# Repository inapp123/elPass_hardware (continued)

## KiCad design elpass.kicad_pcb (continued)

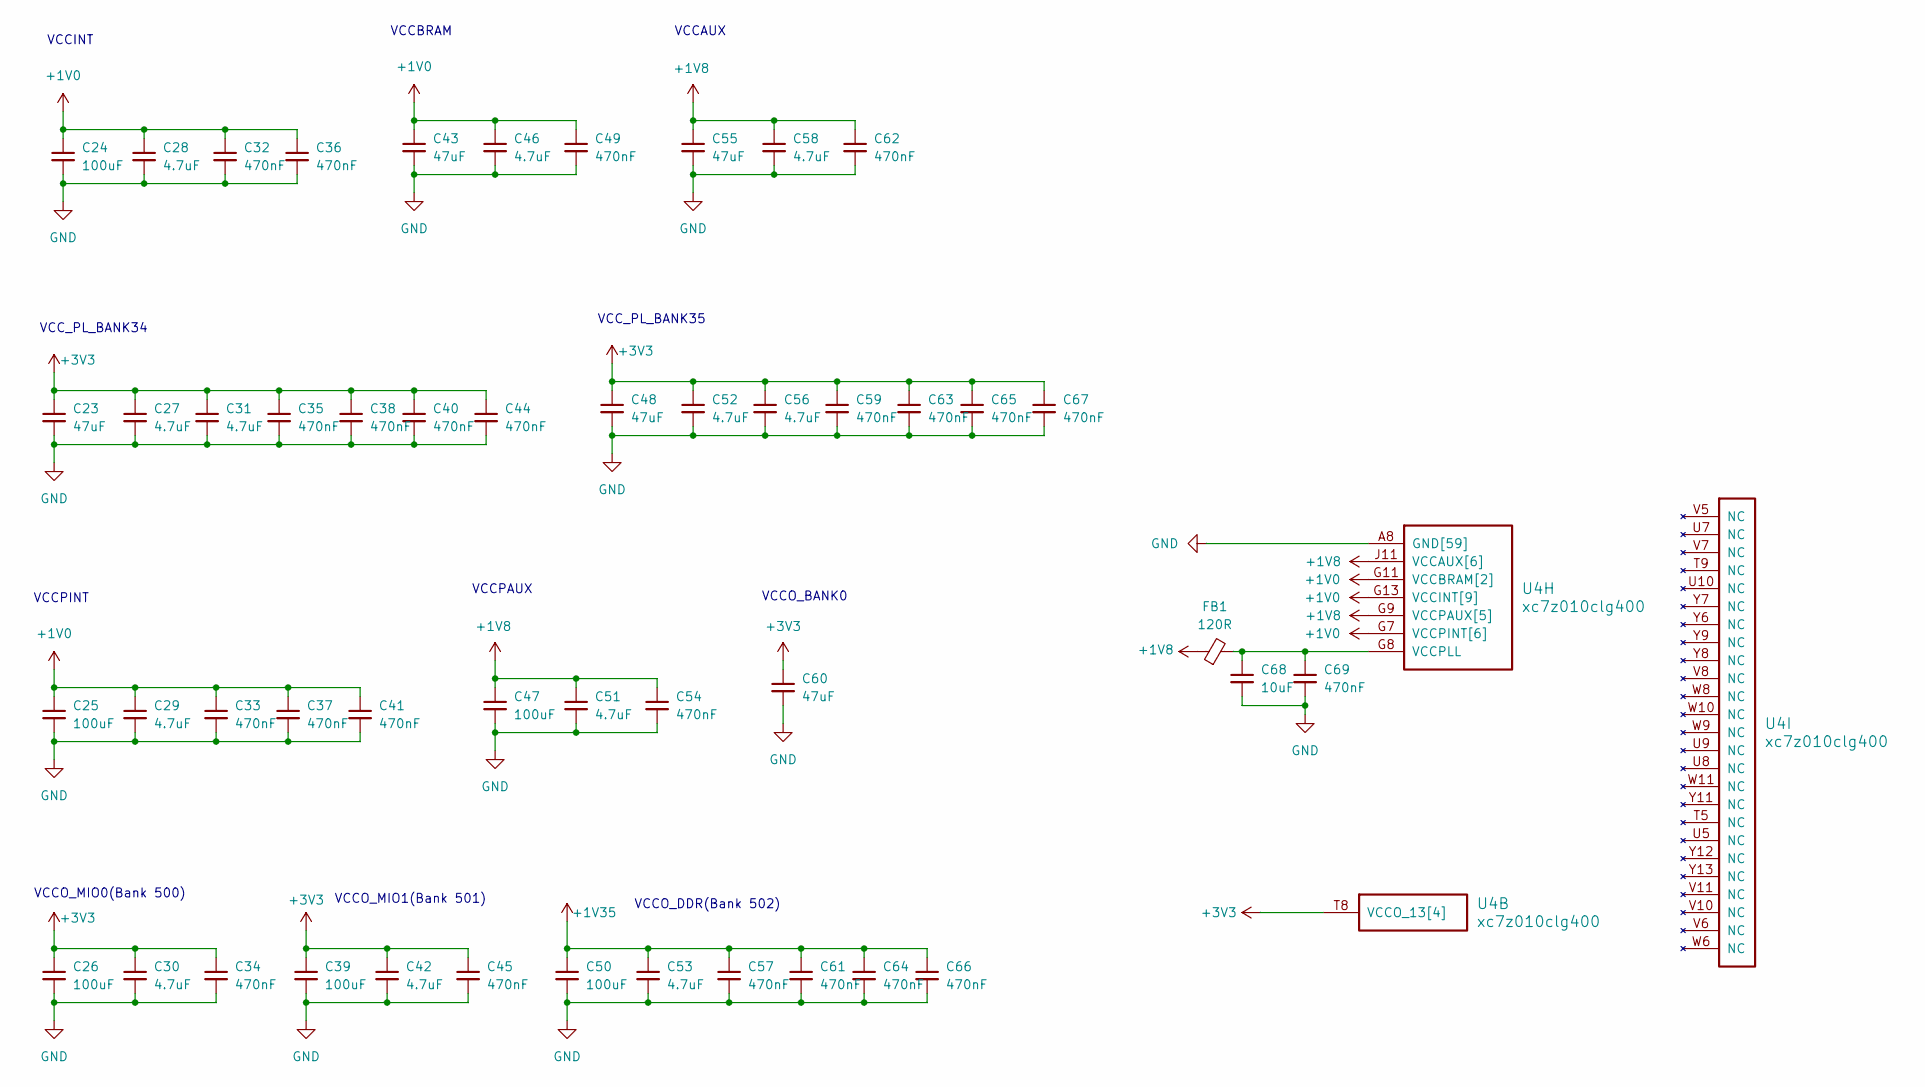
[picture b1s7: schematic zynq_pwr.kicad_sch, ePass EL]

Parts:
C23, C43, C48, C55, C60: 47uF; C_0603_1608Metric
C24, C25, C26, C39, C47, C50: 100uF; C_1206_3216Metric
C27, C28, C29, C30, C31, C42, C46, C51, C52, C53, C56, C58: 4.7uF; C_0402_1005Metric
C32, C33, C35, C36, C37, C38, C40, C41, C44, C45, C49, C54, C57, C59, C61, C62, C63, C64, C65, C67, C69: 470nF; C_0201_0603Metric
C34, C66: 470nF; C_0201_0603Metric_WideGap
C68: 10uF; C_0805_2012Metric
FB1: 120R; L_0603_1608Metric
U4: xc7z010clg400; Xilinx_CLG400_NoPaste_JLC_Package_Delay

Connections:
+1V0: C24.1, C25.1, C28.1, C29.1, C32.1, C33.1, C36.1, C37.1, C41.1, C43.1, C46.1, C49.1, U4.G7 (VCCPINT[6]), U4.G11 (VCCBRAM[2]), U4.G13 (VCCINT[9]), U4.H10 (VCCBRAM[2]), U4.H12 (VCCINT[9]), U4.J7 (VCCPINT[6]), U4.J13 (VCCINT[9]), U4.K12 (VCCINT[9]), U4.L7 (VCCPINT[6]), U4.L13 (VCCINT[9]), U4.M12 (VCCINT[9]), U4.N7 (VCCPINT[6]), U4.N13 (VCCINT[9]), U4.P8 (VCCPINT[6]), U4.P12 (VCCINT[9]), U4.R7 (VCCPINT[6]), U4.R13 (VCCINT[9]); also elsewhere on the board
+1V8: C47.1, C51.1, C54.1, C55.1, C58.1, C62.1, FB1.1, U4.F8 (VCCPAUX[5]), U4.G9 (VCCPAUX[5]), U4.H8 (VCCPAUX[5]), U4.J11 (VCCAUX[6]), U4.K8 (VCCPAUX[5]), U4.L11 (VCCAUX[6]), U4.M8 (VCCPAUX[5]), U4.N9 (VCCAUX[6]), U4.N11 (VCCAUX[6]), U4.P10 (VCCAUX[6]), U4.R9 (VCCAUX[6]); also elsewhere on the board
+1V35: C50.1, C53.1, C57.1, C61.1, C64.1, C66.1; also elsewhere on the board
+3V3: C23.1, C26.1, C27.1, C30.1, C31.1, C34.1, C35.1, C38.1, C39.1, C40.1, C42.1, C44.1, C45.1, C48.1, C52.1, C56.1, C59.1, C60.1, C63.1, C65.1, C67.1, U4.T8 (VCCO_13[4]), U4.U11 (VCCO_13[4]), U4.W7 (VCCO_13[4]), U4.Y10 (VCCO_13[4]); also elsewhere on the board
GND: C23.2, C24.2, C25.2, C26.2, C27.2, C28.2, C29.2, C30.2, C31.2, C32.2, C33.2, C34.2, C35.2, C36.2, C37.2, C38.2, C39.2, C40.2, C41.2, C42.2, C43.2, C44.2, C45.2, C46.2, C47.2, C48.2, C49.2, C50.2, C51.2, C52.2, C53.2, C54.2, C55.2, C56.2, C57.2, C58.2, C59.2, C60.2, C61.2, C62.2, C63.2, C64.2, C65.2, C66.2, C67.2, C68.2, C69.2, U4.A8 (GND[59]), U4.A18 (GND[59]), U4.B1 (GND[59]), U4.B11 (GND[59]), U4.C4 (GND[59]), U4.C9 (GND[59]), U4.C14 (GND[59]), U4.D17 (GND[59]), U4.E10 (GND[59]), U4.E20 (GND[59]), U4.F3 (GND[59]), U4.F7 (GND[59]), U4.G10 (GND[59]), U4.G12 (GND[59]), U4.G16 (GND[59]), U4.H7 (GND[59]), U4.H9 (GND[59]), U4.H11 (GND[59]), U4.H13 (GND[59]), U4.H19 (GND[59]), U4.J2 (GND[59]), U4.J8 (GND[59]), U4.J12 (GND[59]), U4.K5 (GND[59]), U4.K7 (GND[59]), U4.K11 (GND[59]), U4.K13 (GND[59]), U4.K15 (GND[59]), U4.L8 (GND[59]), U4.L12 (GND[59]), U4.L18 (GND[59]), U4.M1 (GND[59]), U4.M7 (GND[59]), U4.M11 (GND[59]), U4.M13 (GND[59]), U4.N4 (GND[59]), U4.N8 (GND[59]), U4.N10 (GND[59]), U4.N12 (GND[59]), U4.N14 (GND[59]), U4.P7 (GND[59]), U4.P9 (GND[59]), U4.P11 (GND[59]), U4.P13 (GND[59]), U4.P17 (GND[59]), U4.R8 (GND[59]), U4.R12 (GND[59]), U4.R20 (GND[59]), U4.T3 (GND[59]), U4.T7 (GND[59]), U4.T13 (GND[59]), U4.U6 (GND[59]), U4.U16 (GND[59]), U4.V9 (GND[59]), U4.V19 (GND[59]), U4.W2 (GND[59]), U4.W12 (GND[59]), U4.Y5 (GND[59]), U4.Y15 (GND[59]); also elsewhere on the board
unnamed: C68.1, C69.1, FB1.2, U4.G8 (VCCPLL)

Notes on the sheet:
VCCO_DDR(Bank 502)
VCCBRAM
VCC_PL_BANK34
VCCPINT
VCCINT
VCCAUX
VCCO_MIO0(Bank 500)
VCCO_BANK0
VCCPAUX
VCCO_MIO1(Bank 501)
VCC_PL_BANK35

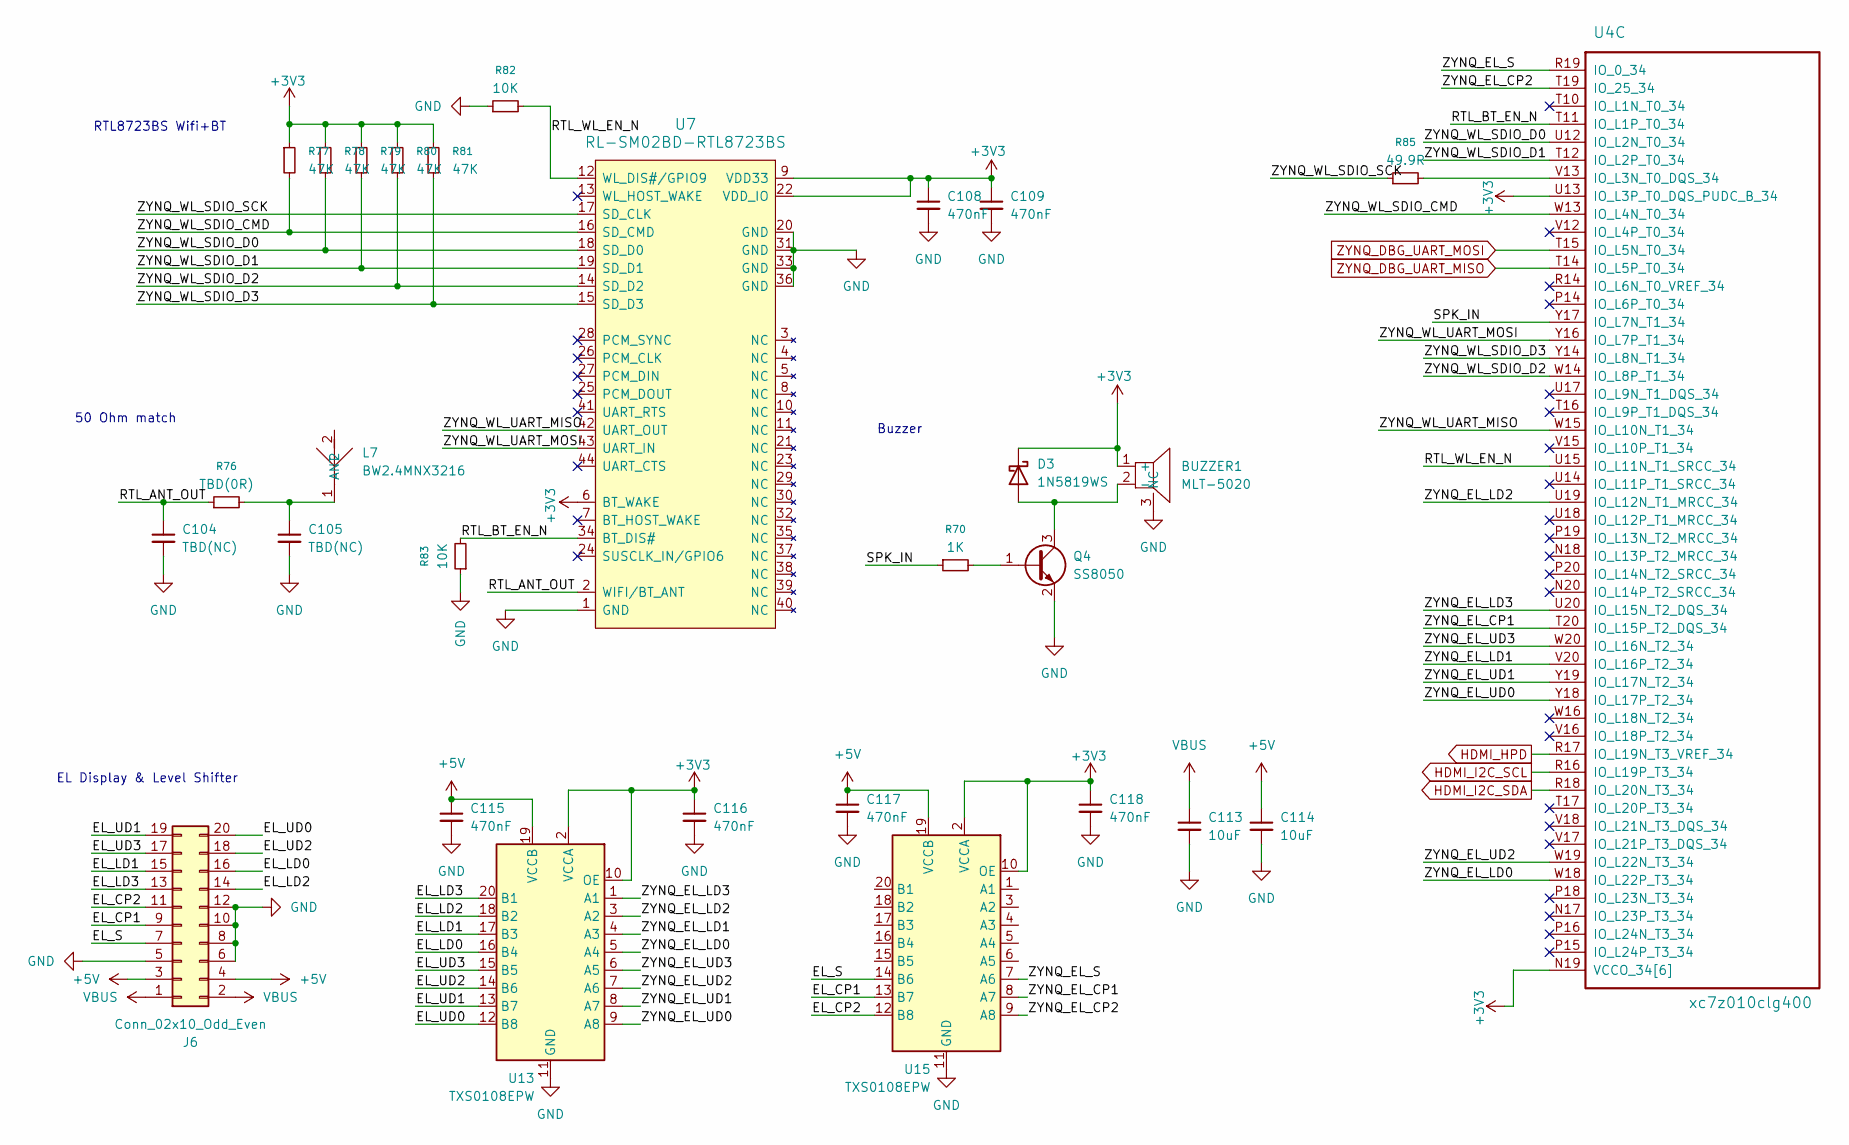
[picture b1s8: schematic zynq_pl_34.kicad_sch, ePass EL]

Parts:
BUZZER1: MLT-5020; BUZ-SMD_L5.0-W5.5-P4.60; MPN MLT-5020; LCSC Part C94598
C104, C105: TBD(NC); C_0402_1005Metric
C108, C109, C115, C116, C117, C118: 470nF; C_0201_0603Metric
C113, C114: 10uF; C_0805_2012Metric
D3: 1N5819WS; D_SOD-323
J6: Conn_02x10_Odd_Even; PinSocket_2x10_P2.00mm_Vertical
L7: BW2.4MNX3216; ANT-SMD_L3.4-W1.8_BW2.4MNX3216; MPN BW2.4MNX3216; LCSC Part C49330090
Q4: SS8050; SOT-23
R70: 1K; R_0402_1005Metric
R76: TBD(0R); R_0402_1005Metric
R77, R78, R79, R80, R81: 47K; R_0402_1005Metric
R82, R83: 10K; R_0402_1005Metric
R85: 49.9R; R_0402_1005Metric
U4: xc7z010clg400; Xilinx_CLG400_NoPaste_JLC_Package_Delay
U7: RL-SM02BD-RTL8723BS; WIRELM-SMD_RL-SM02BD-RTL8723BS; MPN RTL8723BS
U13, U15: TXS0108EPW; TSSOP-20_4.4x6.5mm_P0.65mm

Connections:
+3V3: BUZZER1.1 (+), C108.1, C109.1, C116.1, C118.1, D3.1 (K), R77.1, R78.1, R79.1, R80.1, R81.1, U4.N19 (VCCO_34[6]), U4.R15 (VCCO_34[6]), U4.T18 (VCCO_34[6]), U4.U13 (IO_L3P_T0_DQS_PUDC_B_34), U4.V14 (VCCO_34[6]), U4.W17 (VCCO_34[6]), U4.Y20 (VCCO_34[6]), U7.6 (BT_WAKE), U7.9 (VDD33), U7.22 (VDD_IO), U13.2 (VCCA), U13.10 (OE), U15.2 (VCCA), U15.10 (OE); also elsewhere on the board
+5V: C114.1, C115.1, C117.1, J6.3, J6.4, U13.19 (VCCB), U15.19 (VCCB); also elsewhere on the board
/zynq_pl_34/EL_CP1: J6.9, U15.13 (B7)
/zynq_pl_34/EL_CP2: J6.11, U15.12 (B8)
/zynq_pl_34/EL_LD0: J6.16, U13.16 (B4)
/zynq_pl_34/EL_LD1: J6.15, U13.17 (B3)
/zynq_pl_34/EL_LD2: J6.14, U13.18 (B2)
/zynq_pl_34/EL_LD3: J6.13, U13.20 (B1)
/zynq_pl_34/EL_S: J6.7, U15.14 (B6)
/zynq_pl_34/EL_UD0: J6.20, U13.12 (B8)
/zynq_pl_34/EL_UD1: J6.19, U13.13 (B7)
/zynq_pl_34/EL_UD2: J6.18, U13.14 (B6)
/zynq_pl_34/EL_UD3: J6.17, U13.15 (B5)
/zynq_pl_34/RTL_ANT_OUT: C104.1, R76.1, U7.2 (WIFI/BT_ANT)
/zynq_pl_34/RTL_BT_EN_N: R83.2, U4.T11 (IO_L1P_T0_34), U7.34 (BT_DIS#)
/zynq_pl_34/RTL_WL_EN_N: R82.2, U4.U15 (IO_L11N_T1_SRCC_34), U7.12 (WL_DIS#/GPIO9)
/zynq_pl_34/SPK_IN: R70.1, U4.Y17 (IO_L7N_T1_34)
/zynq_pl_34/ZYNQ_EL_CP1: U4.T20 (IO_L15P_T2_DQS_34), U15.8 (A7)
/zynq_pl_34/ZYNQ_EL_CP2: U4.T19 (IO_25_34), U15.9 (A8)
/zynq_pl_34/ZYNQ_EL_LD0: U4.W18 (IO_L22P_T3_34), U13.5 (A4)
/zynq_pl_34/ZYNQ_EL_LD1: U4.V20 (IO_L16P_T2_34), U13.4 (A3)
/zynq_pl_34/ZYNQ_EL_LD2: U4.U19 (IO_L12N_T1_MRCC_34), U13.3 (A2)
/zynq_pl_34/ZYNQ_EL_LD3: U4.U20 (IO_L15N_T2_DQS_34), U13.1 (A1)
/zynq_pl_34/ZYNQ_EL_S: U4.R19 (IO_0_34), U15.7 (A6)
/zynq_pl_34/ZYNQ_EL_UD0: U4.Y18 (IO_L17P_T2_34), U13.9 (A8)
/zynq_pl_34/ZYNQ_EL_UD1: U4.Y19 (IO_L17N_T2_34), U13.8 (A7)
/zynq_pl_34/ZYNQ_EL_UD2: U4.W19 (IO_L22N_T3_34), U13.7 (A6)
/zynq_pl_34/ZYNQ_EL_UD3: U4.W20 (IO_L16N_T2_34), U13.6 (A5)
/zynq_pl_34/ZYNQ_WL_SDIO_CMD: R77.2, U4.W13 (IO_L4N_T0_34), U7.16 (SD_CMD)
/zynq_pl_34/ZYNQ_WL_SDIO_D0: R78.2, U4.U12 (IO_L2N_T0_34), U7.18 (SD_D0)
/zynq_pl_34/ZYNQ_WL_SDIO_D1: R79.2, U4.T12 (IO_L2P_T0_34), U7.19 (SD_D1)
/zynq_pl_34/ZYNQ_WL_SDIO_D2: R80.2, U4.W14 (IO_L8P_T1_34), U7.14 (SD_D2)
/zynq_pl_34/ZYNQ_WL_SDIO_D3: R81.2, U4.Y14 (IO_L8N_T1_34), U7.15 (SD_D3)
/zynq_pl_34/ZYNQ_WL_SDIO_SCK: R85.1, U7.17 (SD_CLK)
/zynq_pl_34/ZYNQ_WL_UART_MISO: U4.W15 (IO_L10N_T1_34), U7.42 (UART_OUT)
/zynq_pl_34/ZYNQ_WL_UART_MOSI: U4.Y16 (IO_L7P_T1_34), U7.43 (UART_IN)
GND: BUZZER1.3 (NC), C104.2, C105.2, C108.2, C109.2, C113.2, C114.2, C115.2, C116.2, C117.2, C118.2, J6.5, J6.6, J6.8, J6.10, J6.12, Q4.2 (E), R82.1, R83.1, U7.1 (GND), U7.20 (GND), U7.31 (GND), U7.33 (GND), U7.36 (GND), U13.11 (GND), U15.11 (GND); also elsewhere on the board
HDMI_HPD: U4.R17 (IO_L19N_T3_VREF_34); also elsewhere on the board
HDMI_I2C_SCL: U4.R16 (IO_L19P_T3_34); also elsewhere on the board
HDMI_I2C_SDA: U4.R18 (IO_L20N_T3_34); also elsewhere on the board
unnamed: BUZZER1.2 (-), D3.2 (A), Q4.3 (C)
unnamed: C105.1, L7.1 (ANT_1), R76.2
unnamed: Q4.1 (B), R70.2
unnamed: R85.2, U4.V13 (IO_L3N_T0_DQS_34)
VBUS: C113.1, J6.1, J6.2; also elsewhere on the board
ZYNQ_DBG_UART_MISO: U4.T14 (IO_L5P_T0_34); also elsewhere on the board
ZYNQ_DBG_UART_MOSI: U4.T15 (IO_L5N_T0_34); also elsewhere on the board

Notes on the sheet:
EL Display & Level Shifter
50 Ohm match
RTL8723BS Wifi+BT
Buzzer

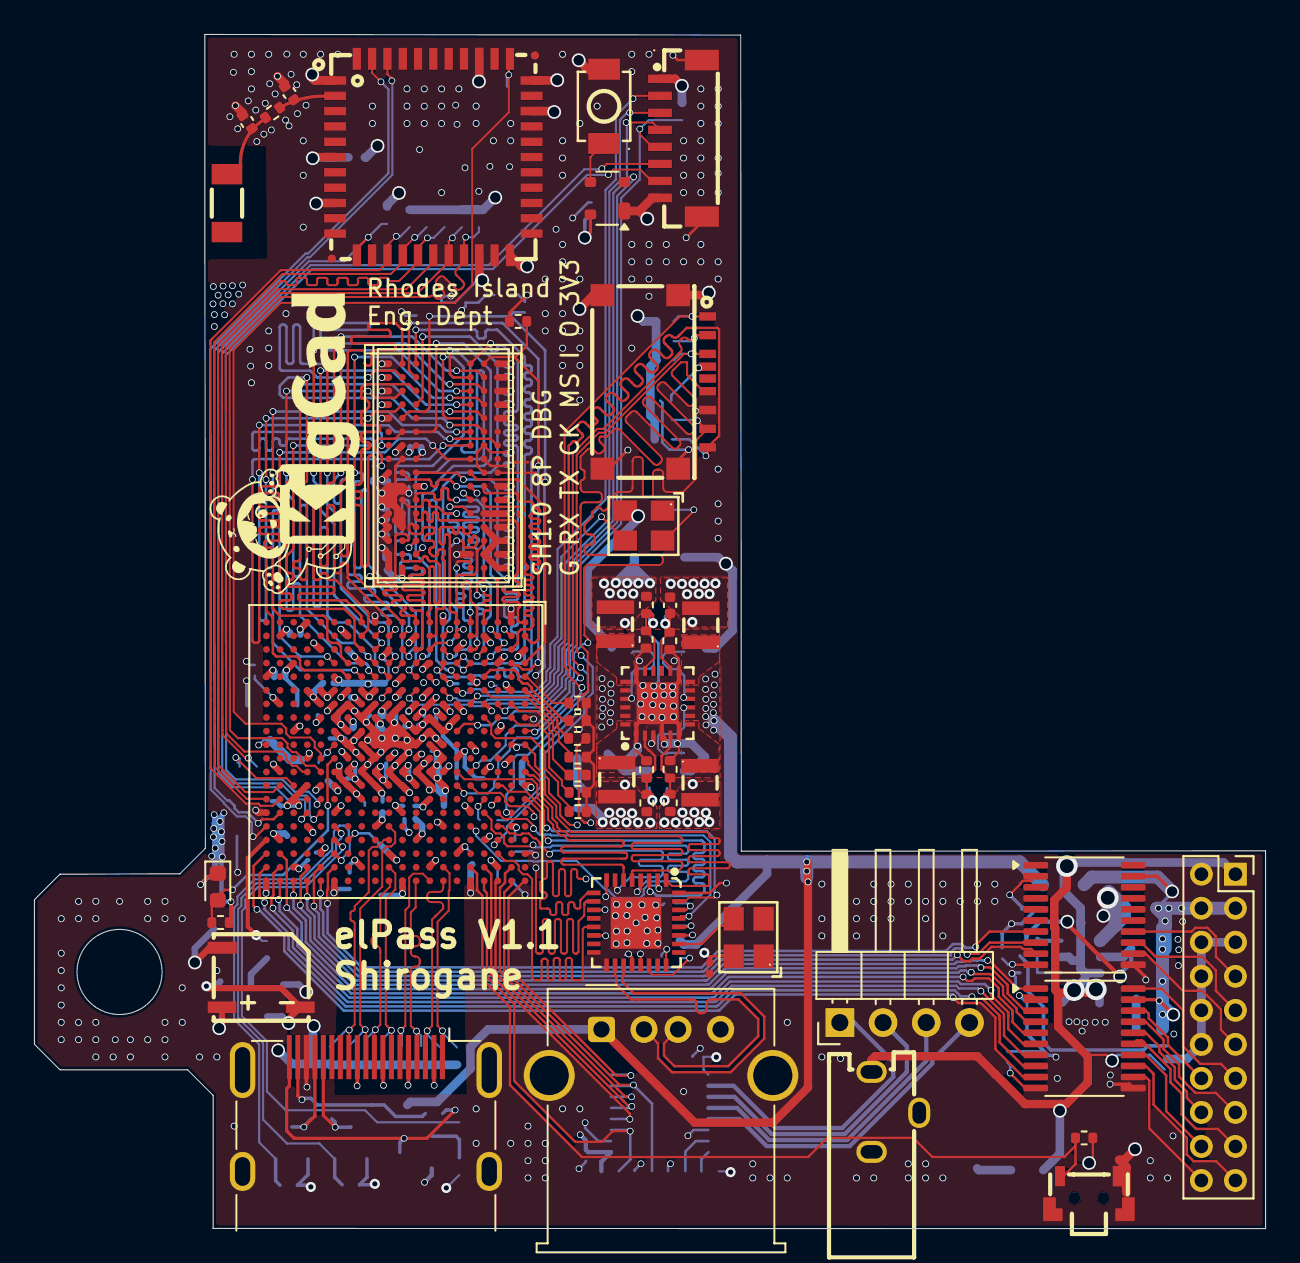
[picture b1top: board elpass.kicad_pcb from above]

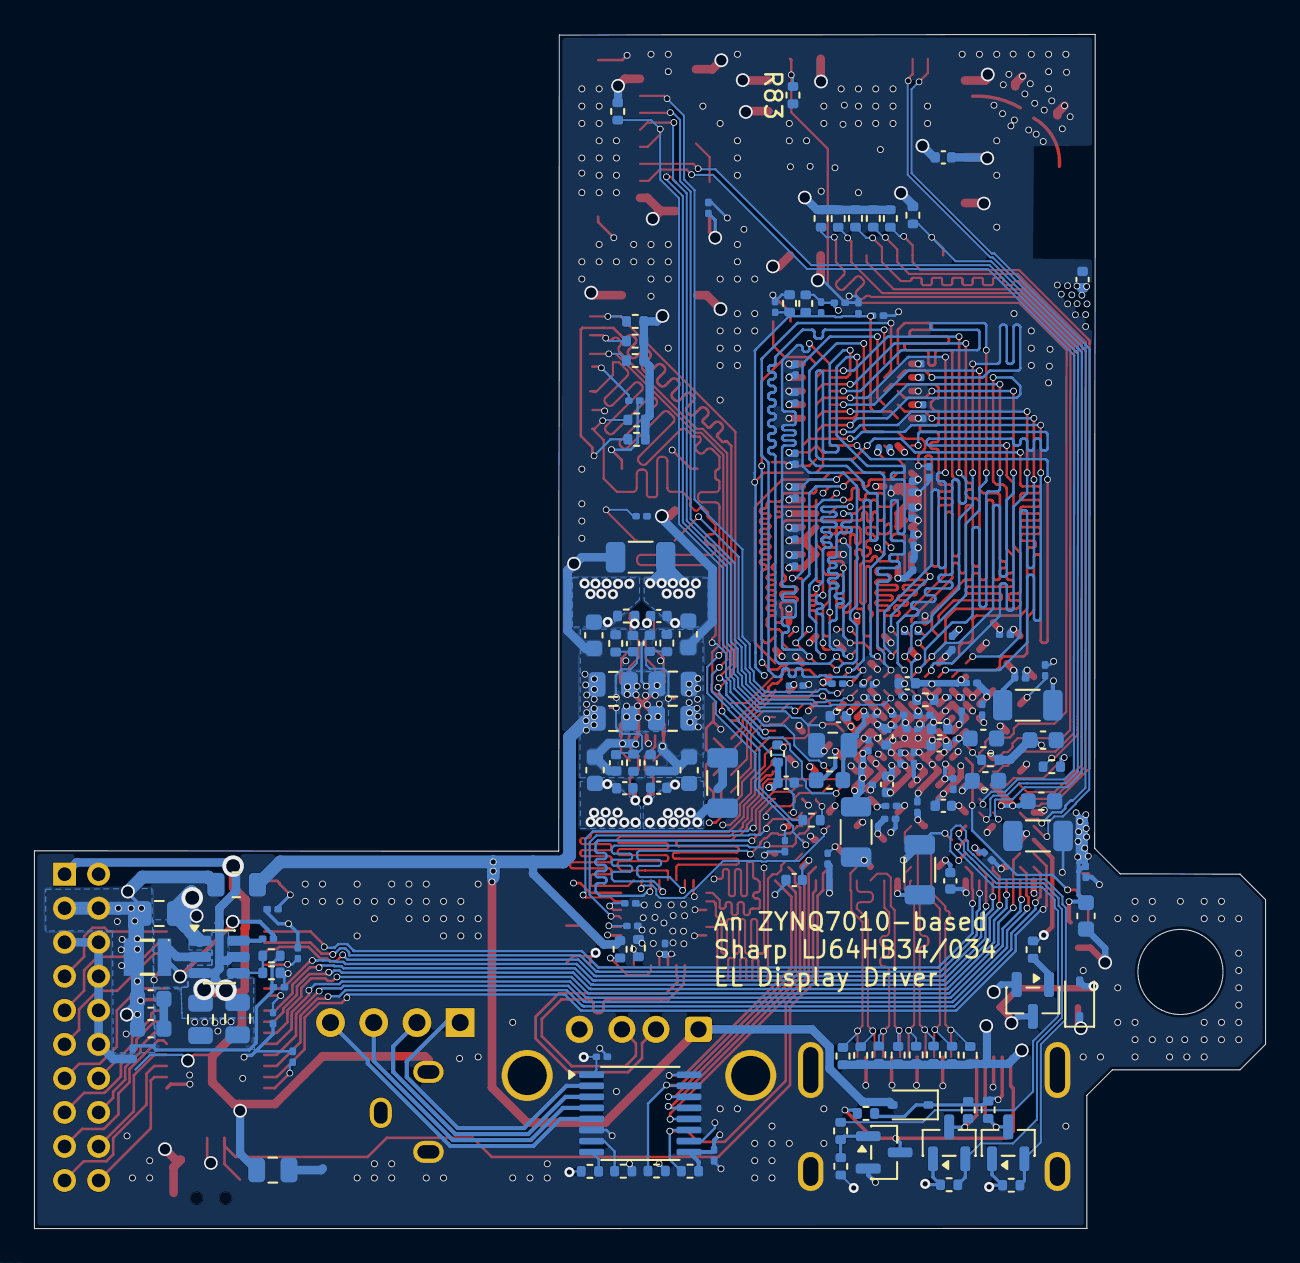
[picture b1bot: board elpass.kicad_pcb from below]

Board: 4 copper layers, 72.4 x 70.2 mm, 213 parts (165 on the bottom side), 186 nets.

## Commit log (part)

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2026-06-30 V1 initial release.
2026-06-30 add readme and licens
